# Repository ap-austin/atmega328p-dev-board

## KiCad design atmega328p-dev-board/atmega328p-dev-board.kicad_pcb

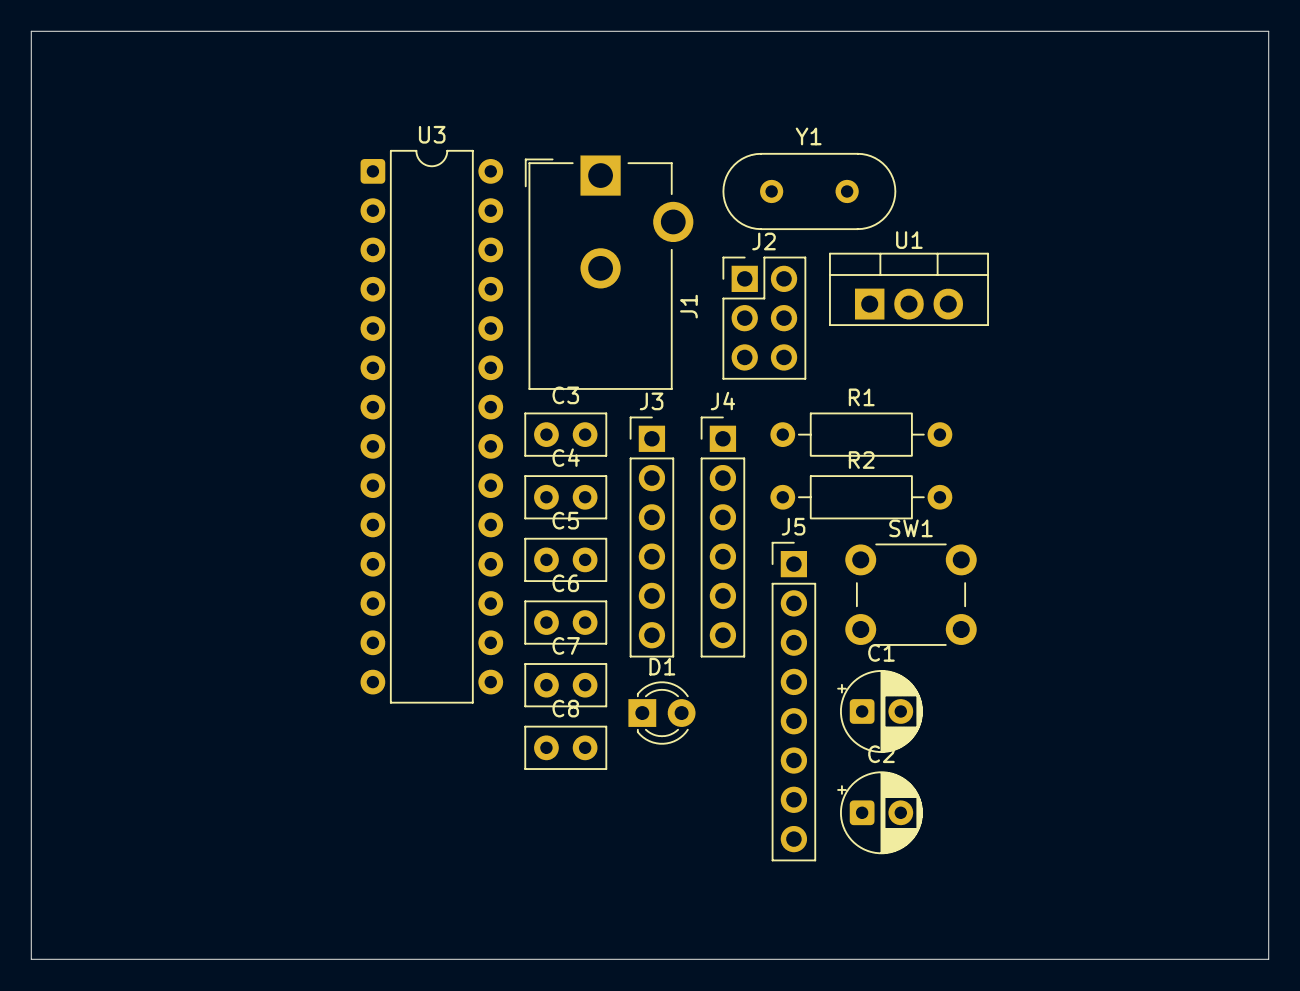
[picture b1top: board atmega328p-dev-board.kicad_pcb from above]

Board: 2 copper layers, 80.0 x 60.0 mm, 20 parts (0 on the bottom side), 25 nets, no tracks yet.

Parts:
C1, C2: 10u; CP_Radial_D5.0mm_P2.50mm
C3, C4, C7, C8: 0.1u; C_Disc_D5.0mm_W2.5mm_P2.50mm
C5, C6: 22p; C_Disc_D5.0mm_W2.5mm_P2.50mm
D1: LED; LED_D3.0mm
J1: Barrel_Jack_Switch; BarrelJack_CUI_PJ-102AH_Horizontal
J2: Conn_02x03_Odd_Even; PinHeader_2x03_P2.54mm_Vertical
J3, J4: Conn_01x06; PinHeader_1x06_P2.54mm_Vertical
J5: Conn_01x08; PinHeader_1x08_P2.54mm_Vertical
R1: 330; R_Axial_DIN0207_L6.3mm_D2.5mm_P10.16mm_Horizontal
R2: 10k; R_Axial_DIN0207_L6.3mm_D2.5mm_P10.16mm_Horizontal
SW1: SW_Push; SW_PUSH_6mm_H5mm
U1: LM7805_TO220; TO-220-3_Vertical
U3: ATmega8-16A; DIP-28_W7.62mm
Y1: 16MHz; Crystal_HC49-U_Vertical

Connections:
+5V: C2.1, C3.1, C8.1, J2.2, R1.1, R2.2, U1.3 (VO), U3.4 (VCC), U3.6 (VCC), U3.18 (AVCC)
GND: C1.2, C2.2, C3.2, C4.2, C5.2, C6.2, C7.1, C8.2, D1.1 (K), J1.2, J1.3, J2.6, SW1.2, U1.2 (GND), U3.3 (GND), U3.5 (GND), U3.21 (AGND)
unnamed: D1.2 (A), R1.2
unnamed: J2.1, J3.5, U3.16 (PB4)
unnamed: J2.3, J3.6, U3.17 (PB5)
unnamed: J2.4, J3.4, U3.15 (PB3)
unnamed: J3.1, U3.12 (PB0)
unnamed: J3.2, U3.13 (PB1)
unnamed: J3.3, U3.14 (PB2)
unnamed: J4.1, U3.23 (PC0)
unnamed: J4.2, U3.24 (PC1)
unnamed: J4.3, U3.25 (PC2)
unnamed: J4.4, U3.26 (PC3)
unnamed: J4.5, U3.27 (PC4)
unnamed: J4.6, U3.28 (PC5)
unnamed: J5.4, U3.1 (PD3)
unnamed: J5.5, U3.2 (PD4)
unnamed: J5.6, U3.9 (PD5)
unnamed: J5.7, U3.10 (PD6)
unnamed: J5.8, U3.11 (PD7)
unnamed: C1.1, C4.1, J1.1, U1.1 (VI)
unnamed: C7.2, U3.20 (AREF)
unnamed: C6.1, U3.7 (PB6/XTAL1), Y1.1
unnamed: C5.1, U3.8 (PB7/XTAL2), Y1.2
RST: J2.5, R2.1, SW1.1
